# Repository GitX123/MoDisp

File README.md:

# MoDisp
Robust and flexible modular display system which reconfigures data paths upon hardware change

[back-end]
* Run on Raspberry Pi or C.H.I.P., act as a gateway between the web UI and the MoDisp protocol.
* Mainly contributed by e841018, and also thanks HongCheng Zheng for developing the prototype of the UI.

[controller]
* Run on ATMEGA 328
* James Chan contributed to the firmware, while e841018 designed the PCB.

[bracket]
* Designed by Onshape, publicly available at
  https://cad.onshape.com/documents/cf011c8e0843ee4877112711/w/4f09f0267c82e90f73bca7a8/e/ec47567f47b796b4294d7e92

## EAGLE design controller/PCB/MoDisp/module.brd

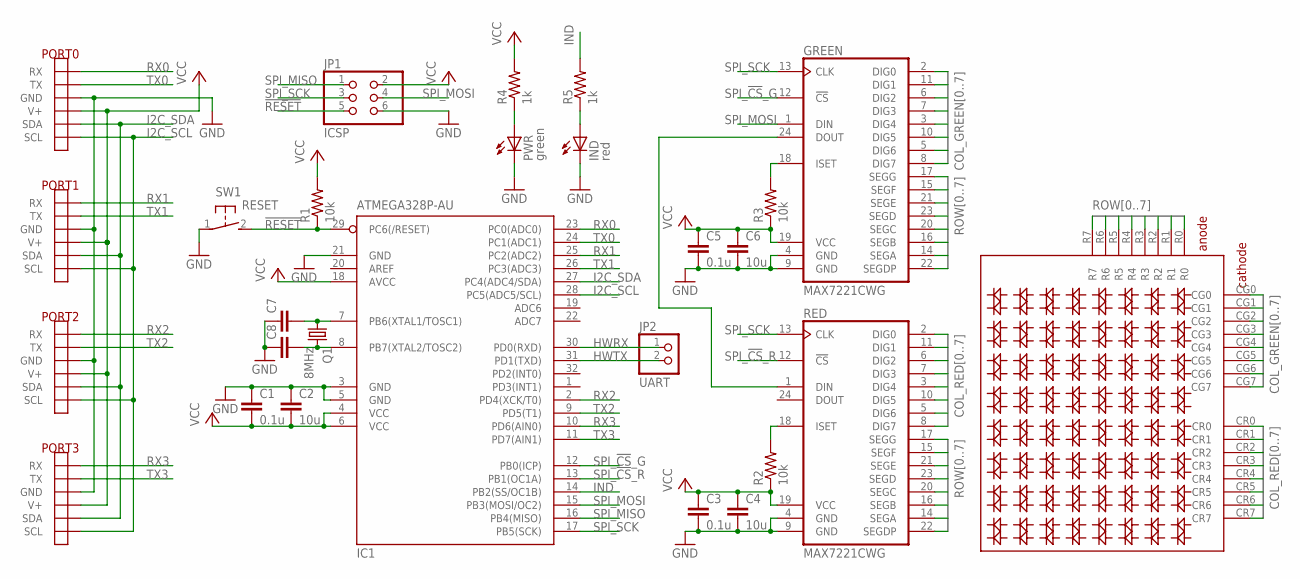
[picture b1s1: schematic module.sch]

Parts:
C1, C3, C5: 0.1u; C0805
C2, C4, C6: 10u; C1206
C7, C8: C-EUC0805; C0805
GREEN: MAX7221CWG; SO24L
IC1: ATMEGA328P-AU; TQFP32-08
IND: red; CHIPLED_0805
JP1: ICSP; 2X03
JP2: UART; 1X02
PORT0, PORT1, PORT2, PORT3: PORT
PWR: green; CHIPLED_0805
Q1: 8MHz; HC49UP
R1, R2, R3: 10k; R0805
R4, R5: 1k; R0805
RED: MAX7221CWG; SO24L
SW1: RESET; DTSM-3
U$2: 88LED_MATRIX_BICOLOR_ROW_ANODE; 8*8LED_MATRIX_BICOLOR_ROW_ANODE

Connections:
!RESET!: IC1.29 (PC6(/RESET)), JP1.5, R1.1, SW1.2
COL_GREEN0: GREEN.2 (DIG0), U$2.CG0
COL_GREEN1: GREEN.11 (DIG1), U$2.CG1
COL_GREEN2: GREEN.6 (DIG2), U$2.CG2
COL_GREEN3: GREEN.7 (DIG3), U$2.CG3
COL_GREEN4: GREEN.3 (DIG4), U$2.CG4
COL_GREEN5: GREEN.10 (DIG5), U$2.CG5
COL_GREEN6: GREEN.5 (DIG6), U$2.CG6
COL_GREEN7: GREEN.8 (DIG7), U$2.CG7
COL_RED0: RED.2 (DIG0), U$2.CR0
COL_RED1: RED.11 (DIG1), U$2.CR1
COL_RED2: RED.6 (DIG2), U$2.CR2
COL_RED3: RED.7 (DIG3), U$2.CR3
COL_RED4: RED.3 (DIG4), U$2.CR4
COL_RED5: RED.10 (DIG5), U$2.CR5
COL_RED6: RED.5 (DIG6), U$2.CR6
COL_RED7: RED.8 (DIG7), U$2.CR7
GND: C1.1, C2.1, C3.2, C4.2, C5.2, C6.2, C7.1, C8.1, GREEN.4 (GND), GREEN.9 (GND), IC1.3 (GND), IC1.5 (GND), IC1.21 (GND), IND.C, JP1.6, PORT0.GND_L (GND), PORT0.GND_L_D (GND), PORT0.GND_R (GND), PORT0.GND_R_D (GND), PORT1.GND_L (GND), PORT1.GND_L_D (GND), PORT1.GND_R (GND), PORT1.GND_R_D (GND), PORT2.GND_L (GND), PORT2.GND_L_D (GND), PORT2.GND_R (GND), PORT2.GND_R_D (GND), PORT3.GND_L (GND), PORT3.GND_L_D (GND), PORT3.GND_R (GND), PORT3.GND_R_D (GND), PWR.C, RED.4 (GND), RED.9 (GND), SW1.1
HWRX: IC1.30 (PD0(RXD)), JP2.1
HWTX: IC1.31 (PD1(TXD)), JP2.2
I2C_SCL: IC1.28 (PC5(ADC5/SCL)), PORT0.SCL_L (SCL), PORT0.SCL_L_D (SCL), PORT0.SCL_R (SCL), PORT0.SCL_R_D (SCL), PORT1.SCL_L (SCL), PORT1.SCL_L_D (SCL), PORT1.SCL_R (SCL), PORT1.SCL_R_D (SCL), PORT2.SCL_L (SCL), PORT2.SCL_L_D (SCL), PORT2.SCL_R (SCL), PORT2.SCL_R_D (SCL), PORT3.SCL_L (SCL), PORT3.SCL_L_D (SCL), PORT3.SCL_R (SCL), PORT3.SCL_R_D (SCL)
I2C_SDA: IC1.27 (PC4(ADC4/SDA)), PORT0.SDA_L (SDA), PORT0.SDA_L_D (SDA), PORT0.SDA_R (SDA), PORT0.SDA_R_D (SDA), PORT1.SDA_L (SDA), PORT1.SDA_L_D (SDA), PORT1.SDA_R (SDA), PORT1.SDA_R_D (SDA), PORT2.SDA_L (SDA), PORT2.SDA_L_D (SDA), PORT2.SDA_R (SDA), PORT2.SDA_R_D (SDA), PORT3.SDA_L (SDA), PORT3.SDA_L_D (SDA), PORT3.SDA_R (SDA), PORT3.SDA_R_D (SDA)
IND: IC1.14 (PB2(SS/OC1B)), R5.2
unnamed: C7.2, IC1.7 (PB6(XTAL1/TOSC1)), Q1.1
unnamed: C8.2, IC1.8 (PB7(XTAL2/TOSC2)), Q1.2
unnamed: GREEN.18 (ISET), R3.2
unnamed: GREEN.24 (DOUT), RED.1 (DIN)
unnamed: PWR.A, R4.1
unnamed: IND.A, R5.1
unnamed: R2.2, RED.18 (ISET)
ROW0: GREEN.17 (SEGG), RED.17 (SEGG), U$2.R0
ROW1: GREEN.15 (SEGF), RED.15 (SEGF), U$2.R1
ROW2: GREEN.21 (SEGE), RED.21 (SEGE), U$2.R2
ROW3: GREEN.23 (SEGD), RED.23 (SEGD), U$2.R3
ROW4: GREEN.20 (SEGC), RED.20 (SEGC), U$2.R4
ROW5: GREEN.16 (SEGB), RED.16 (SEGB), U$2.R5
ROW6: GREEN.14 (SEGA), RED.14 (SEGA), U$2.R6
ROW7: GREEN.22 (SEGDP), RED.22 (SEGDP), U$2.R7
RX0: IC1.23 (PC0(ADC0)), PORT0.RX_L (RX), PORT0.RX_L_D (RX)
RX1: IC1.25 (PC2(ADC2)), PORT1.RX_L (RX), PORT1.RX_L_D (RX)
RX2: IC1.2 (PD4(XCK/T0)), PORT2.RX_L (RX), PORT2.RX_L_D (RX)
RX3: IC1.10 (PD6(AIN0)), PORT3.RX_L (RX), PORT3.RX_L_D (RX)
SPI_!CS!_G: GREEN.12 (!CS!), IC1.12 (PB0(ICP))
SPI_!CS!_R: IC1.13 (PB1(OC1A)), RED.12 (!CS!)
SPI_MISO: IC1.16 (PB4(MISO)), JP1.1
SPI_MOSI: GREEN.1 (DIN), IC1.15 (PB3(MOSI/OC2)), JP1.4
SPI_SCK: GREEN.13 (CLK), IC1.17 (PB5(SCK)), JP1.3, RED.13 (CLK)
TX0: IC1.24 (PC1(ADC1)), PORT0.TX_R (TX), PORT0.TX_R_D (TX)
TX1: IC1.26 (PC3(ADC3)), PORT1.TX_R (TX), PORT1.TX_R_D (TX)
TX2: IC1.9 (PD5(T1)), PORT2.TX_R (TX), PORT2.TX_R_D (TX)
TX3: IC1.11 (PD7(AIN1)), PORT3.TX_R (TX), PORT3.TX_R_D (TX)
VCC: C1.2, C2.2, C3.1, C4.1, C5.1, C6.1, GREEN.19 (VCC), IC1.4 (VCC), IC1.6 (VCC), IC1.18 (AVCC), JP1.2, PORT0.V+_L (V+), PORT0.V+_L_D (V+), PORT0.V+_R (V+), PORT0.V+_R_D (V+), PORT1.V+_L (V+), PORT1.V+_L_D (V+), PORT1.V+_R (V+), PORT1.V+_R_D (V+), PORT2.V+_L (V+), PORT2.V+_L_D (V+), PORT2.V+_R (V+), PORT2.V+_R_D (V+), PORT3.V+_L (V+), PORT3.V+_L_D (V+), PORT3.V+_R (V+), PORT3.V+_R_D (V+), R1.2, R2.1, R3.1, R4.2, RED.19 (VCC)

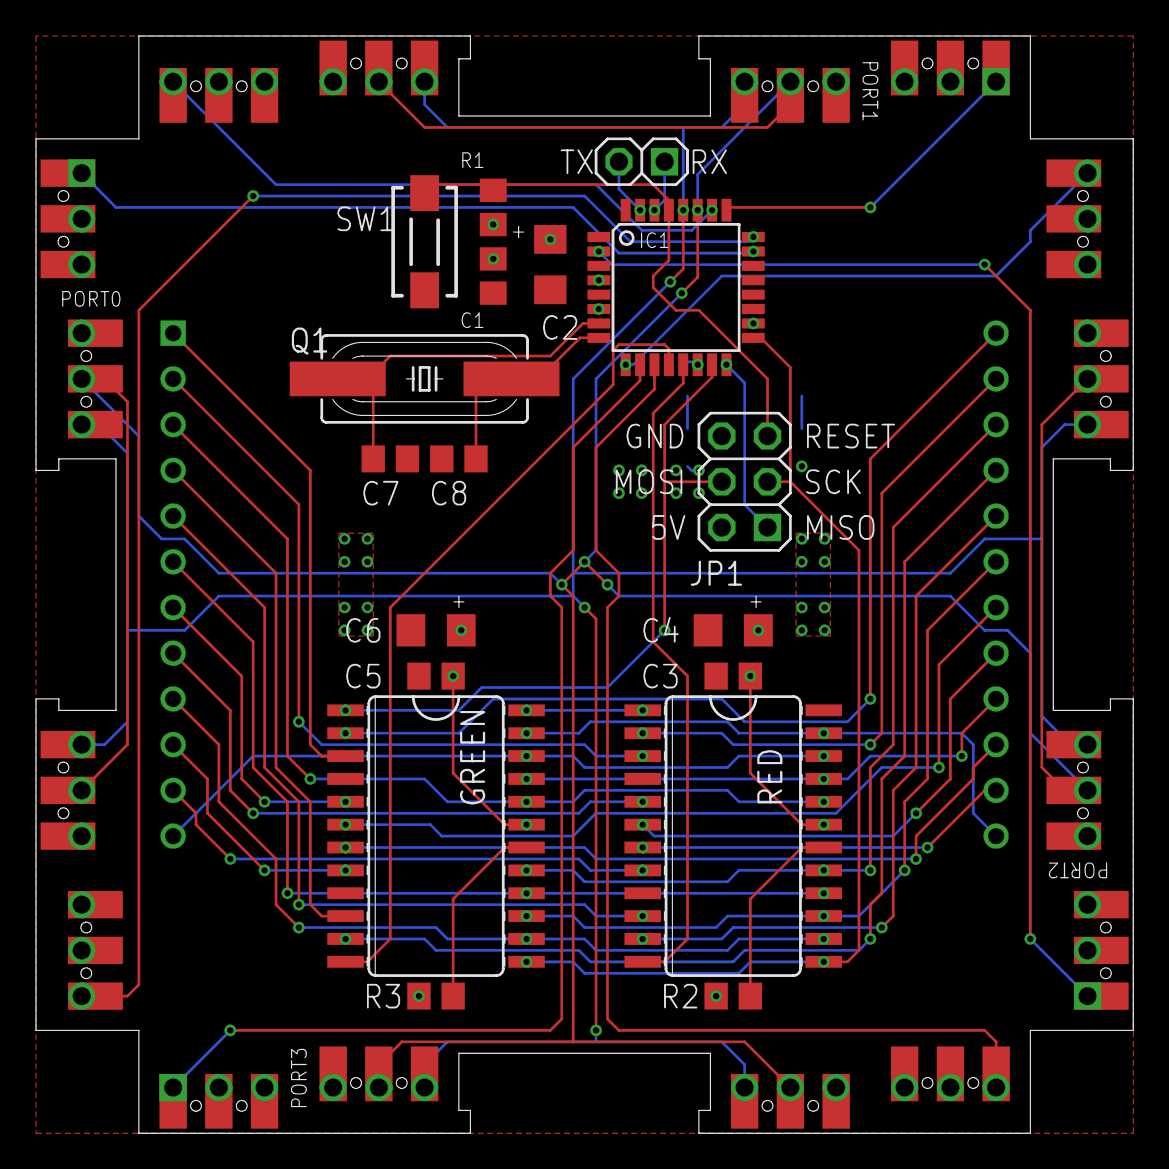
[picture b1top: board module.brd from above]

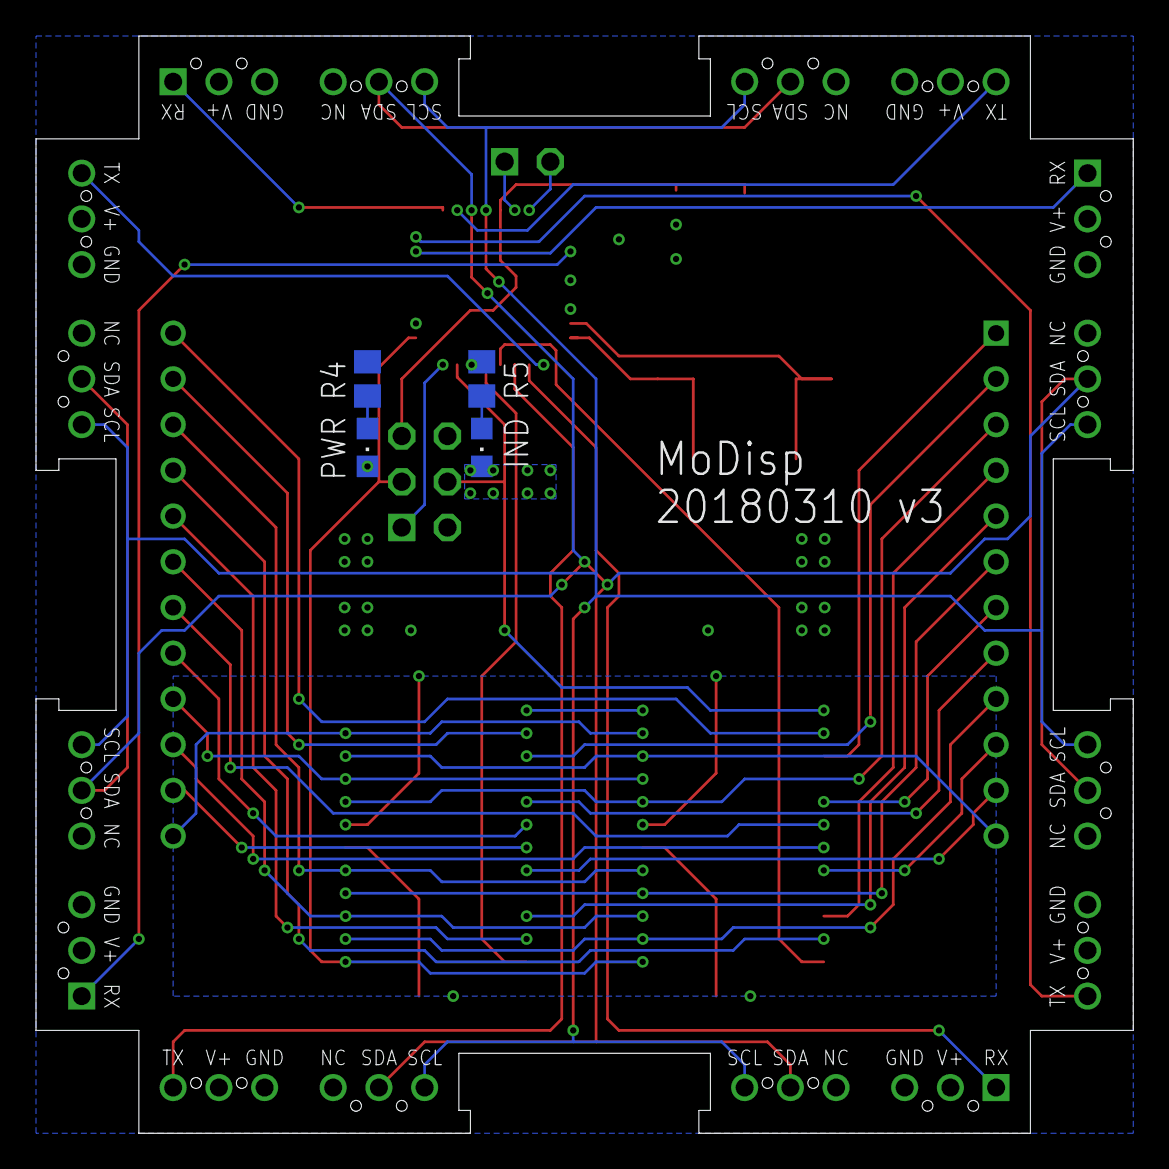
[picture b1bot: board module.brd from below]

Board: 2 copper layers, 61.0 x 61.0 mm, 27 parts (4 on the bottom side), 52 nets.

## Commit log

2019-03-09 20180116 version
2019-03-09 Add files via upload
    20180310 v3
2019-03-09 add link to the bracket design
